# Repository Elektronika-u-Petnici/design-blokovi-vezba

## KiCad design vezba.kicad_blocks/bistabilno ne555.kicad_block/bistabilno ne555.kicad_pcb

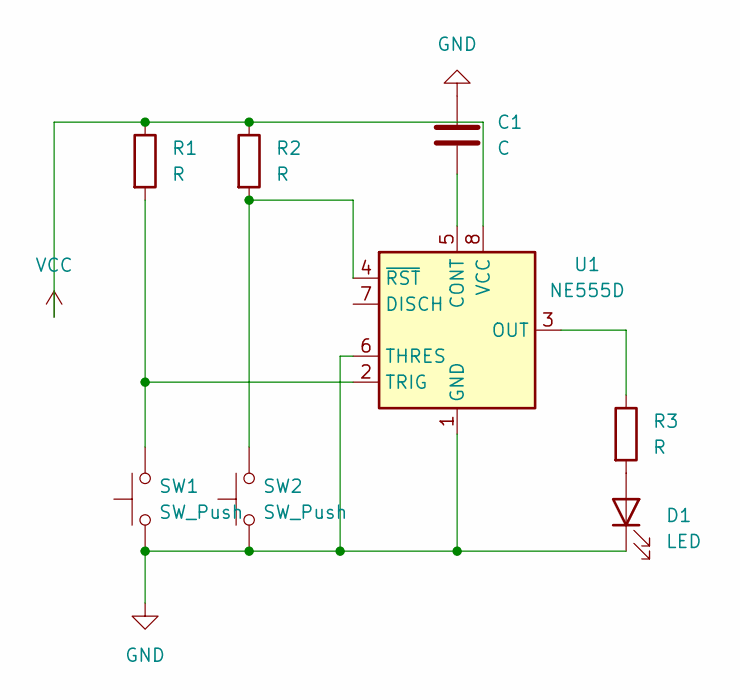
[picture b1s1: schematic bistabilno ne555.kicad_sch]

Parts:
C1: C; C_0805_2012Metric
D1: LED; C_0805_2012Metric_Pad1.18x1.45mm_HandSolder
R1, R2, R3: R; C_0805_2012Metric_Pad1.18x1.45mm_HandSolder
SW1, SW2: SW_Push; C_0805_2012Metric_Pad1.18x1.45mm_HandSolder
U1: NE555D; SOIC-8_3.9x4.9mm_P1.27mm

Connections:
GND: C1.1, D1.1 (K), SW1.1, SW2.1, U1.1 (GND), U1.6 (THRES)
unnamed: D1.2 (A), R3.2
unnamed: C1.2, U1.5 (CONT)
unnamed: R3.1, U1.3 (OUT)
unnamed: R1.2, SW1.2, U1.2 (TRIG)
unnamed: R2.2, SW2.2, U1.4 (~RST)
VCC: R1.1, R2.1, U1.8 (VCC)

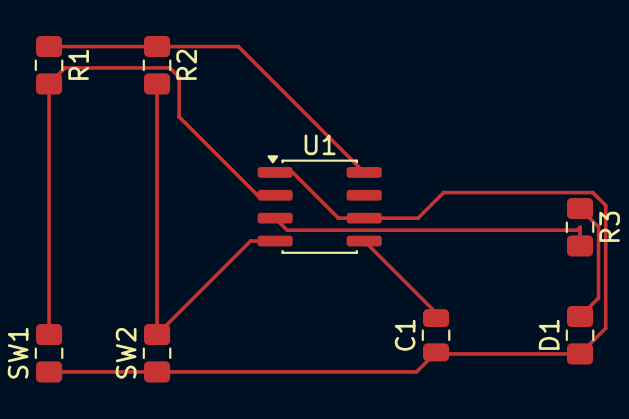
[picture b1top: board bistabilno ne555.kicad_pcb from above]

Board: 2 copper layers, 8 parts (0 on the bottom side), 7 nets.

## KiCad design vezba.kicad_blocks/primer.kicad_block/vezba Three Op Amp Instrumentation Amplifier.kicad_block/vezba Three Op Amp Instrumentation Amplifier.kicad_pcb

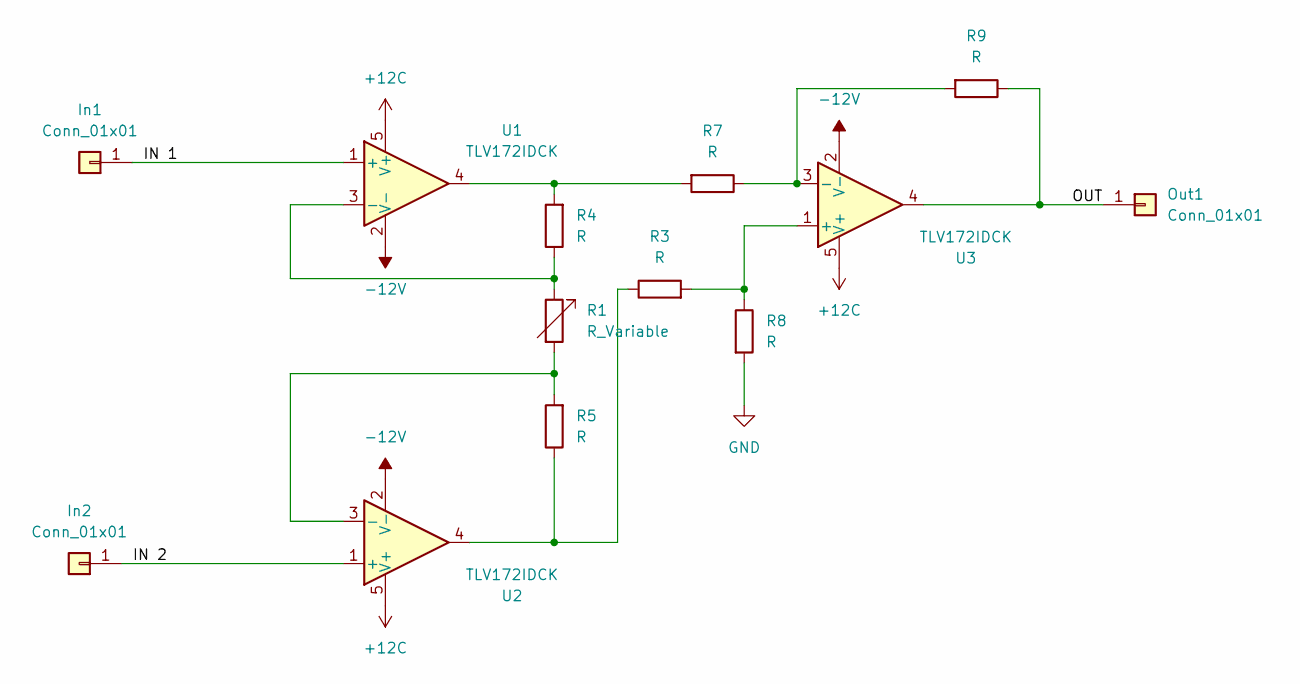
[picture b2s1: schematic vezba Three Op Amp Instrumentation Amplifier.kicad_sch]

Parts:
In1, In2: Conn_01x01; SolderWirePad_1x01_SMD_1x2mm
Out1: Conn_01x01; SolderWirePad_1x01_SMD_1x2mm
R1: R_Variable; Potentiometer_Bourns_3214W_Vertical
R3, R4, R5, R7, R8, R9: R; R_0805_2012Metric
U1, U2, U3: TLV172IDCK; SOT-353_SC-70-5

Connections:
+12C: U1.5 (V+), U2.5 (V+), U3.5 (V+)
-12V: U1.2 (V-), U2.2 (V-), U3.2 (V-)
/IN 1: In1.1 (Pin_1_1), U1.1 (+)
/IN 2: In2.1 (Pin_1_1), U2.1 (+)
/OUT: Out1.1 (Pin_1_1), R9.1, U3.4
GND: R8.2
unnamed: R3.1, R5.1, U2.4
unnamed: R4.2, R7.2, U1.4
unnamed: R1.1, R4.1, U1.3 (-)
unnamed: R1.2, R5.2, U2.3 (-)
unnamed: R3.2, R8.1, U3.1 (+)
unnamed: R7.1, R9.2, U3.3 (-)

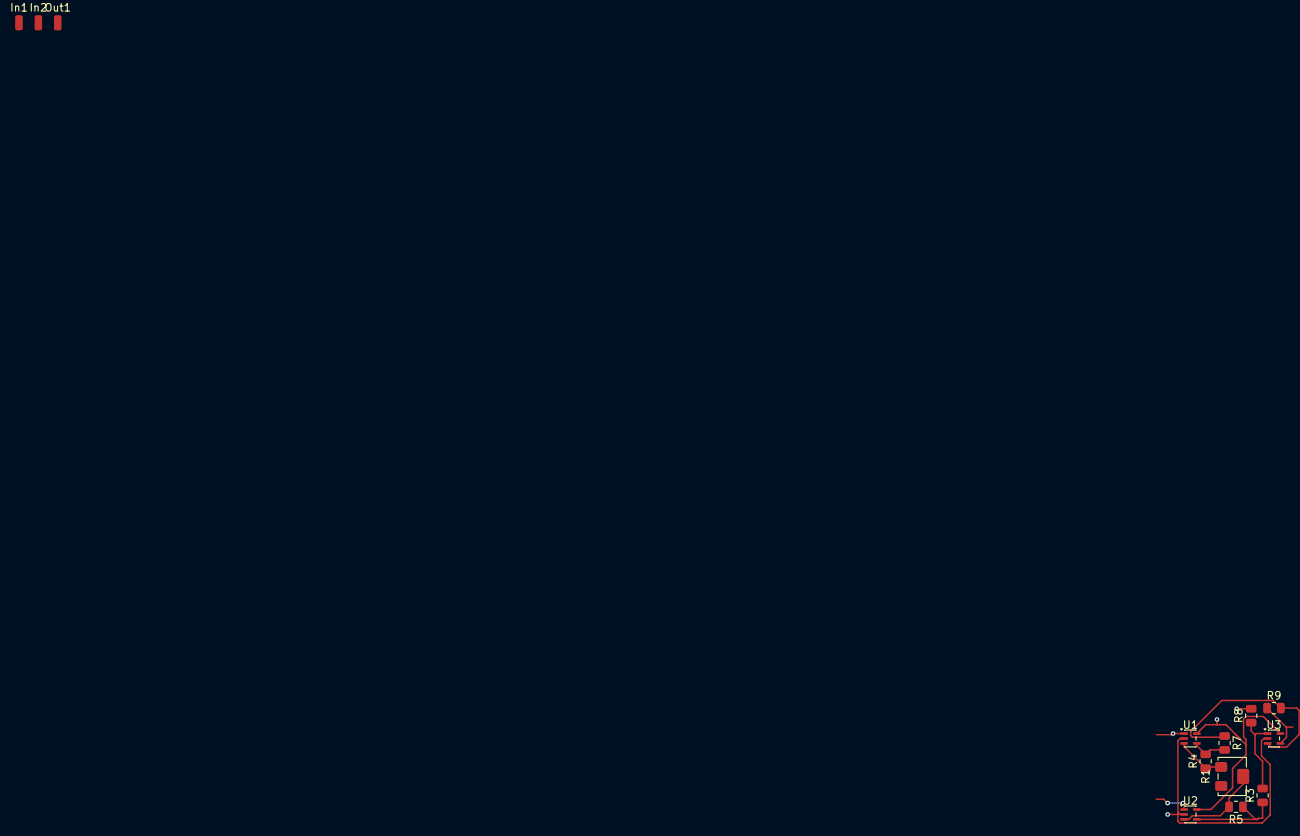
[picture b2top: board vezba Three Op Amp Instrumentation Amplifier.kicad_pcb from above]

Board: 2 copper layers, 13 parts (0 on the bottom side), 11 nets.

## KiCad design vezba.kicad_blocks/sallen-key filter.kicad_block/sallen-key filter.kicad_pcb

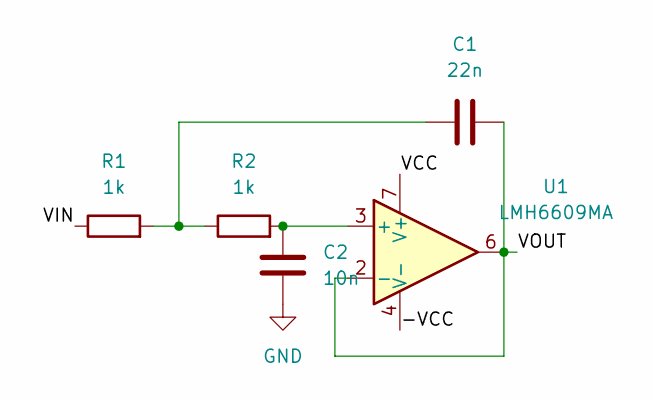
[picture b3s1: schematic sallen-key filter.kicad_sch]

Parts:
C1: 22n; C_0805_2012Metric
C2: 10n; C_0805_2012Metric
R1, R2: 1k; R_0402_1005Metric
U1: LMH6609MA; SOIC-8_3.9x4.9mm_P1.27mm

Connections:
/-VCC: U1.4 (V-)
/VCC: U1.7 (V+)
/VIN: R1.1
/VOUT: C1.2, U1.2 (-), U1.6
GND: C2.1
unnamed: C1.1, R1.2, R2.1
unnamed: C2.2, R2.2, U1.3 (+)

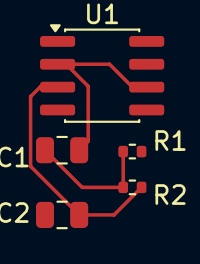
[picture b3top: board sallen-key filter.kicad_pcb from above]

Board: 2 copper layers, 5 parts (0 on the bottom side), 3 nets.

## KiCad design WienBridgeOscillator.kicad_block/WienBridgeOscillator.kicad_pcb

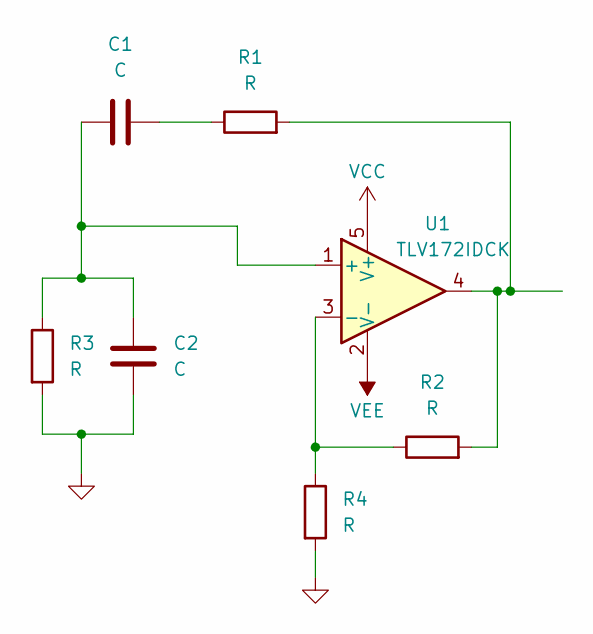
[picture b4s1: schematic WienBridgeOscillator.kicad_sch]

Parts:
C1, C2: C; C_01005_0402Metric
R1, R2, R3, R4: R; R_01005_0402Metric
U1: TLV172IDCK; SOT-353_SC-70-5

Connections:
GND: C2.2, R3.2, R4.2
unnamed: C1.2, R1.1
unnamed: R1.2, R2.2, U1.4
unnamed: C1.1, C2.1, R3.1, U1.1 (+)
unnamed: R2.1, R4.1, U1.3 (-)
VCC: U1.5 (V+)
VEE: U1.2 (V-)

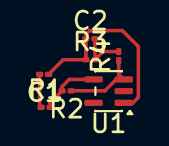
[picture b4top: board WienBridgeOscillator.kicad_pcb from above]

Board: 2 copper layers, 7 parts (0 on the bottom side), 5 nets.

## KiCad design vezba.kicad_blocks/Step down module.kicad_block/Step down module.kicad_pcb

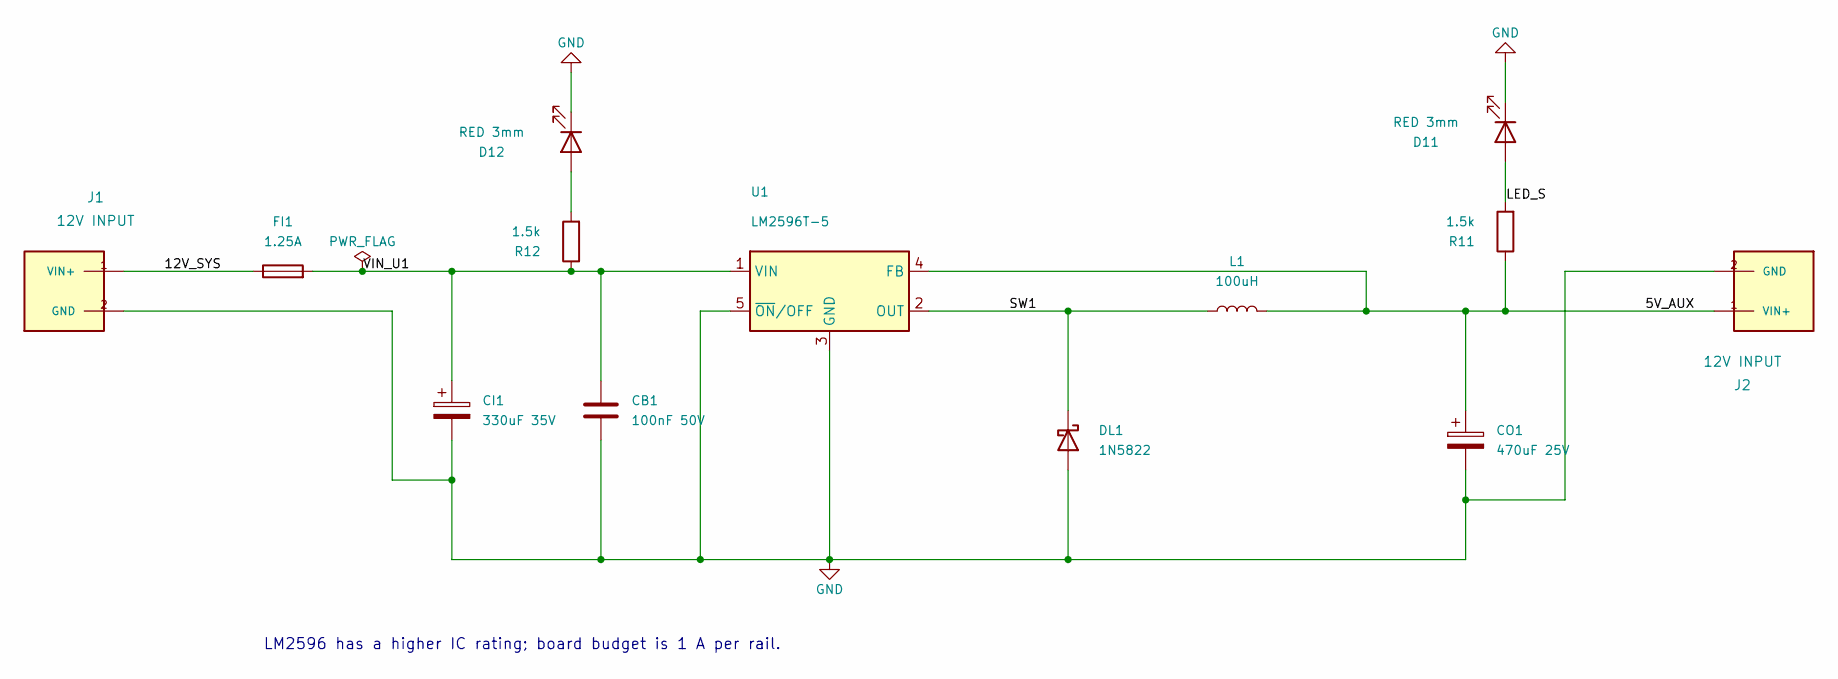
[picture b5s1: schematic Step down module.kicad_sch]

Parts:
CB1: 100nF 50V; C_1206_3216Metric_Pad1.33x1.80mm_HandSolder
CI1: 330uF 35V; CP_Radial_D10.0mm_P5.00mm
CO1: 470uF 25V; CP_Radial_D10.0mm_P5.00mm
D11, D12: RED 3mm; LED_D3.0mm
DL1: 1N5822; D_DO-201AD_P12.70mm_Horizontal
FI1: 1.25A; Fuse_Littelfuse-NANO2-451_453
J1, J2: 12V INPUT; TerminalBlock_MaiXu_MX126-5.0-02P_1x02_P5.00mm
L1: 100uH; L_Bourns_SRR1260
R11, R12: 1.5k; R_0805_2012Metric_Pad1.20x1.40mm_HandSolder
U1: LM2596T-5; TO-220-5_Horizontal_TabUp

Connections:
/5V_AUX: CO1.1, J2.1 (VIN+), L1.2, R11.1, U1.4 (FB)
/12V_SYS: FI1.1, J1.1 (VIN+)
/LED_S: D11.2 (A), R11.2
/SW1: DL1.1 (K), L1.1, U1.2 (OUT)
/VIN_U1: CB1.1, CI1.1, FI1.2, R12.1, U1.1 (VIN)
GND: CB1.2, CI1.2, CO1.2, D11.1 (K), D12.1 (K), DL1.2 (A), J1.2 (GND), J2.2 (GND), U1.3 (GND), U1.5 (~ON/OFF)
unnamed: D12.2 (A), R12.2

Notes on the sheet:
LM2596 has a higher IC rating; board budget is 1 A per rail.

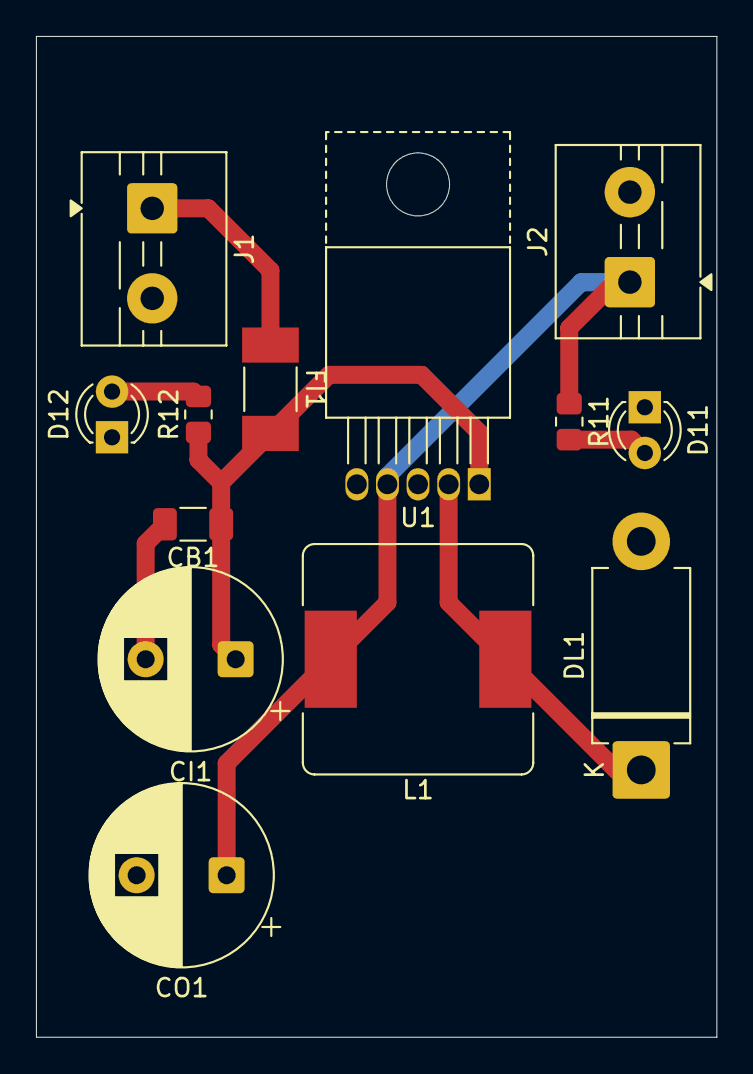
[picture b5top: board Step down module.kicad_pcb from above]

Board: 2 copper layers, 37.8 x 55.6 mm, 13 parts (0 on the bottom side), 7 nets.

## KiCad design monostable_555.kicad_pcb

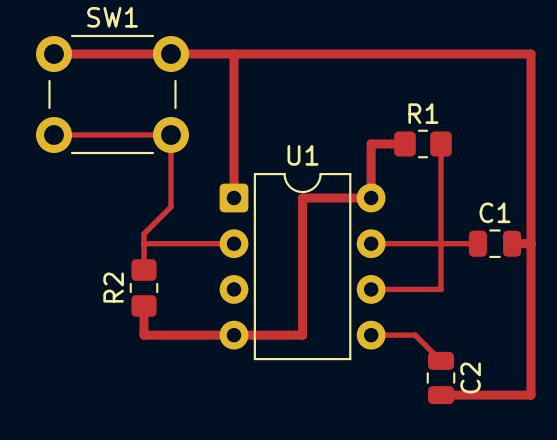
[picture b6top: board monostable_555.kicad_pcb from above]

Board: 2 copper layers, 6 parts (0 on the bottom side), 5 nets.

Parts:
C1: 10uF; C_0805_2012Metric
C2: 10nF; C_0805_2012Metric
R1: 100k; R_0805_2012Metric_Pad1.20x1.40mm_HandSolder
R2: 10k; R_0805_2012Metric_Pad1.20x1.40mm_HandSolder
SW1: start; SW_PUSH_6mm
U1: NE555P; DIP-8_W7.62mm

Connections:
GND: C1.2, C2.2, SW1.1, U1.1
unnamed: C2.1, U1.5
unnamed: C1.1, R1.2, U1.6, U1.7
unnamed: R2.2, SW1.2, U1.2
VCC: R1.1, R2.1, U1.4, U1.8

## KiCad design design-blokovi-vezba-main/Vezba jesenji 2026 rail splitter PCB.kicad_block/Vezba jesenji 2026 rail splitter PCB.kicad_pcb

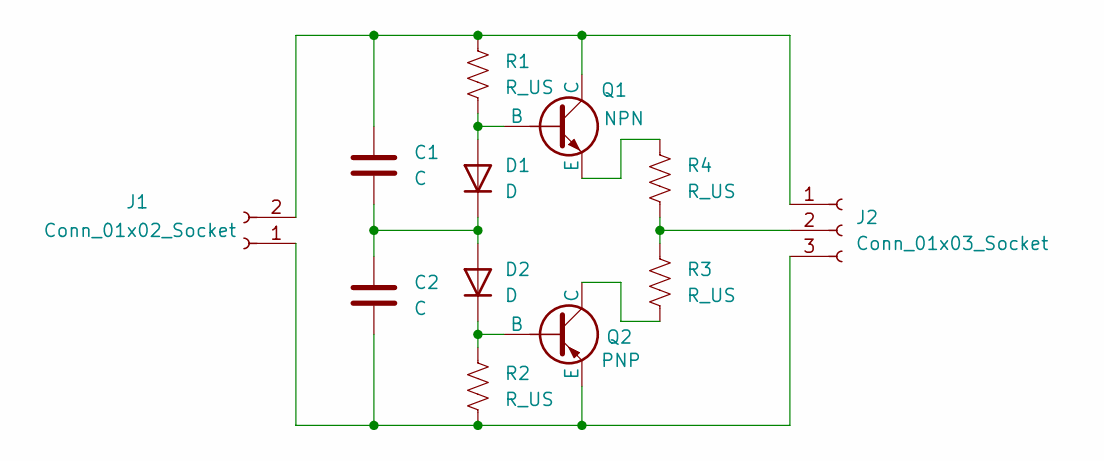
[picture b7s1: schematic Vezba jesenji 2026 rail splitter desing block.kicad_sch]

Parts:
C1, C2: C; C_Radial_D16.0mm_H31.5mm_P7.50mm
D1, D2: D; D_DO-15_P2.54mm_Vertical_AnodeUp
J1: Conn_01x02_Socket; PinHeader_1x02_P2.54mm_Vertical
J2: Conn_01x03_Socket; PinHeader_1x03_P2.54mm_Vertical
Q1: NPN; TO-92L_HandSolder
Q2: PNP; TO-92L_HandSolder
R1, R2, R3, R4: R_US; R_Axial_DIN0617_L17.0mm_D6.0mm_P20.32mm_Horizontal

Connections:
unnamed: D1.2 (A), Q1.2 (B), R1.2
unnamed: C1.1, C2.2, D1.1 (K), D2.2 (A)
unnamed: D2.1 (K), Q2.2 (B), R2.1
unnamed: C2.1, J1.1, J2.3, Q2.3 (E), R2.2
unnamed: C1.2, J1.2, J2.1, Q1.1 (C), R1.1
unnamed: J2.2, R3.1, R4.2
unnamed: Q1.3 (E), R4.1
unnamed: Q2.1 (C), R3.2

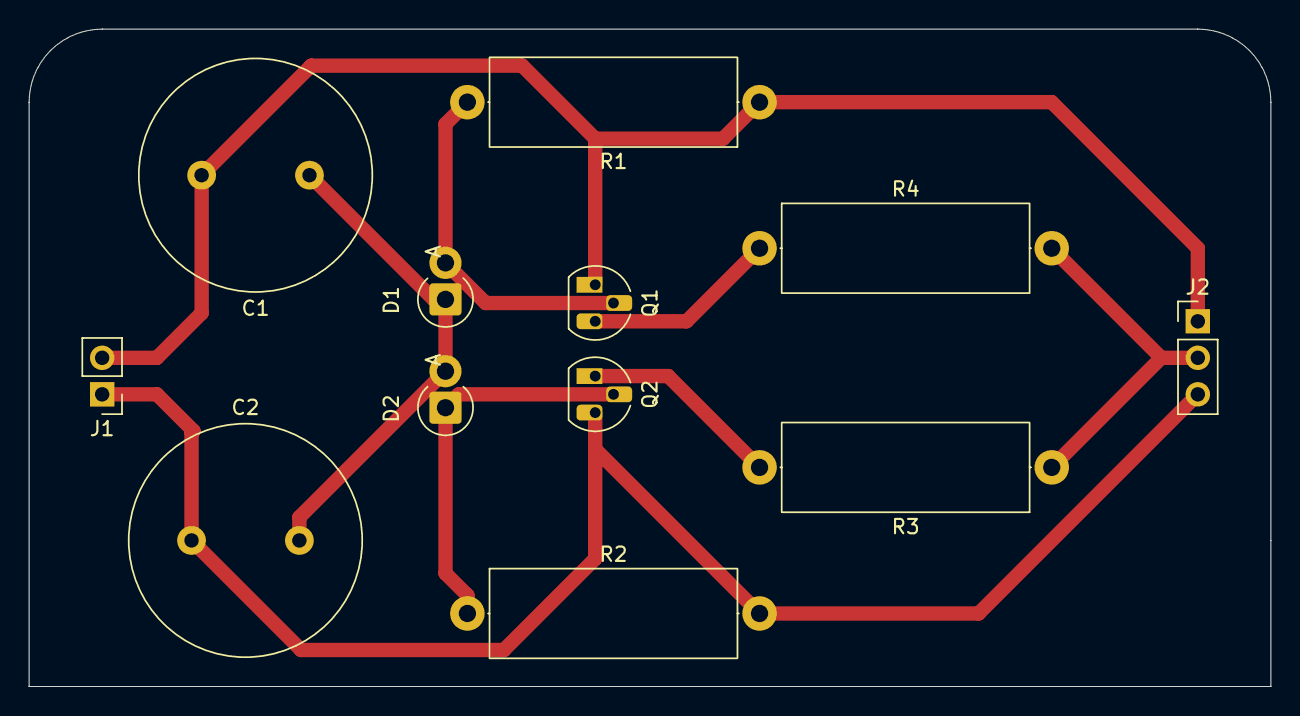
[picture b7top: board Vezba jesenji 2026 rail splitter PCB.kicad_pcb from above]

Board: 2 copper layers, 86.4 x 45.7 mm, 12 parts (0 on the bottom side), 8 nets.
